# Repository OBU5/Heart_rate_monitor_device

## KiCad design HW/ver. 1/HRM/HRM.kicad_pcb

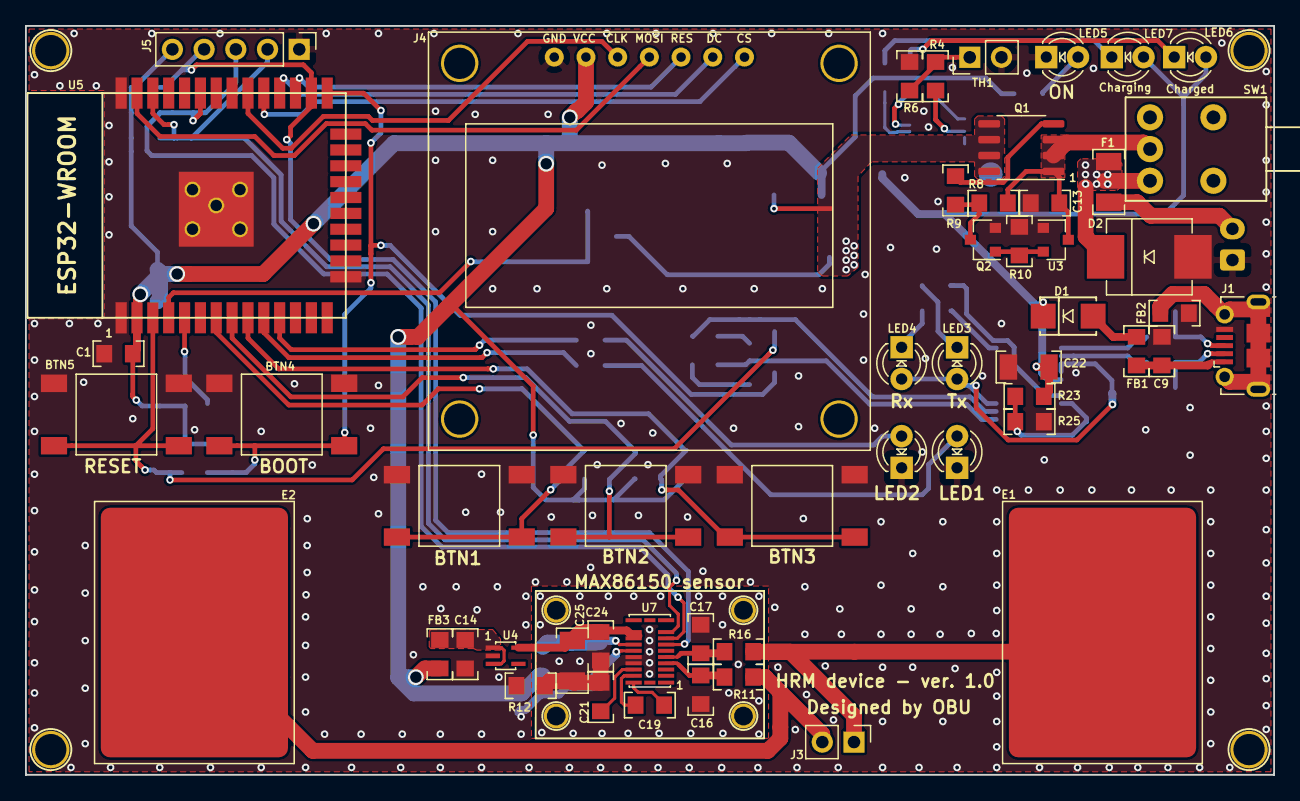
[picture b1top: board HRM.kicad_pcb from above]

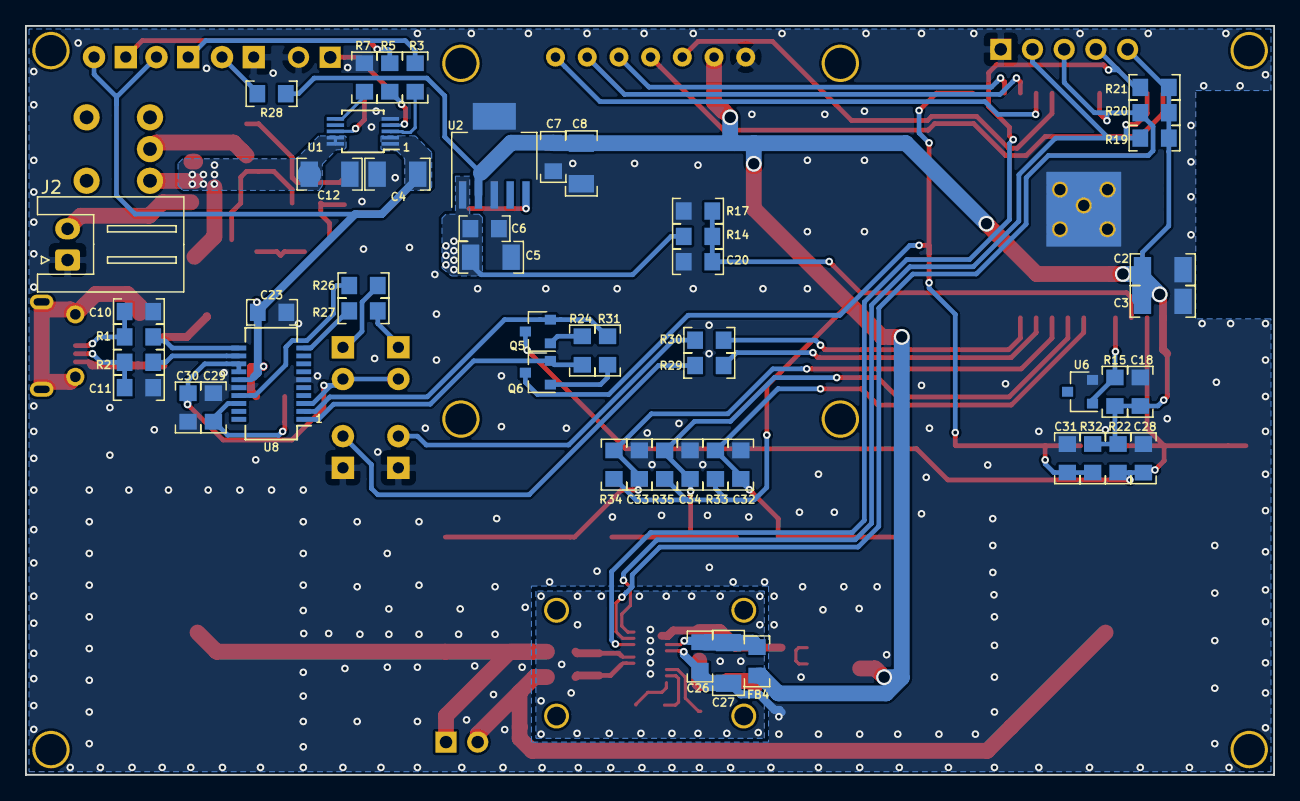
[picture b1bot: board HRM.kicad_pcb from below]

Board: 2 copper layers, 100.0 x 60.0 mm, 114 parts (53 on the bottom side), 65 nets.

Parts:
BTN1, BTN2, BTN3: user button; BTN_6x6mm
BTN4: BOOT; BTN_6x6mm
BTN5: RESET; BTN_6x6mm
C1, C6, C7, C13, C18, C20, C23, C24, C26, C28, C29, C30, C31, C32, C33, C34: 100n; C0805
C2, C3, C4, C5, C8, C12, C22, C25, C27: 10u; C1206
C9: 10n; C0805
C10, C11: 47p; C0805
C14, C19, C21: 1u; C0805
C16, C17: 10p; C0805
D1: D_Schottky; D_SMA
D2: 3A; D_SMC
E1: ECG_P; Electrode
E2: ECG_N; Electrode
F1: Fuse; R1206
FB1, FB2, FB3, FB4: Ferite bead; R0805
J1: USB_B_Micro; USB_Micro-B_Molex-105017-0001
J2: BATT; JST_XH_S2B-XH-A_1x02_P2.50mm_Horizontal
J3: Electrodes; PinHeader_1x02_P2.54mm_Vertical
J4: OLED; 1.3_inch_OLED
J5: I2C; PinHeader_1x05_P2.54mm_Vertical
J6, J8, J10, J12: Screw_Terminal_01x01; Screwh_hole-1.5mm
J7, J9, J11, J13: Screw_Terminal_01x01; Screwh_hole-2.5mm
LED1, LED2: User; LED-THT-3.0mm
LED3: TX; LED-THT-3.0mm
LED4: RX; LED-THT-3.0mm
LED5: Awake; LED-THT-3.0mm
LED6: Charged; LED-THT-3.0mm
LED7: Charging; LED-THT-3.0mm
Q1: PMOS-Si4403DDY; SO-8_3.9x4.9mm_P1.27mm
Q2: BSS138; SOT-23
Q5, Q6: BC847; SOT-23
R1, R2: 27; R0805
R3, R5: 470R; R0805
R4: 1.54k; R0805
R6: 69.8k; R0805
R7, R9, R26, R27, R28, R29, R30: 1k; R0805
R8, R10: 100k; R0805
R11, R16: 50k; R0805
R12: 0; R0805
R14: 13k; R0805
R15: 5k; R0805
R17: 24k; R0805
R19, R20, R21, R23, R24, R31: 4k7; R0805
R22, R25, R32, R33, R34, R35: 10k; R0805
SW1: Power; Switch_P-KNX125
TH1: NTC; PinHeader_1x02_P2.54mm_Vertical
U1: MCP73833-MSOP; MSOP-10_3x3mm_P0.5mm
U2: TPS73733; SOT-223-6
U3: TPS3839K33; SOT-23
U4: MAX8511; SC70-5pin
U5: ESP32-WROOM
U6: LM4040-2.5; SOT-23
U7: MAX86150; OLGA-22pin
U8: FT231XS; SSOP-20_3.9x8.7mm_P0.635mm

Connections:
3V3_IO: C30.2, LED3.2, LED4.2, U8.3, U8.13, U8.14
+1V8: C24.2, C25.2, U4.5, U7.13, U7.14
+3V3: C1.1, C2.1, C3.1, C7.2, C8.2, C18.2, FB3.2, FB4.1, J4.2, J5.5, R15.2, R19.1, R20.1, R21.1, R22.2, R28.2, R32.2, R33.2, R34.2, R35.2, U2.2, U5.2
+5VA: C4.1, C22.2, C23.2, D1.1, LED6.2, LED7.2, R23.2, U1.1, U1.2, U8.15
+BATT: C5.2, C6.2, Q1.5, Q1.6, Q1.7, Q1.8, R14.2, U2.1, U2.5
/BOOT: BTN4.2, C31.2, Q6.3, R32.1, U5.25
/DTR: Q6.2, R24.2, U8.1
/RESET: BTN5.2, C28.2, Q5.3, R22.1, U5.3
/RTS: Q5.2, R31.2, U8.2
/RX_LED: R27.1, U8.10
/TX_LED: R26.1, U8.17
/USBDM: R2.1, U8.12
/USBDP: R1.1, U8.11
/VBUS_SENSE: C29.1, R23.1, R25.2, U8.18
BAT_ADC: C20.2, R14.1, R17.2, U5.4
GNDA: C16.1, C17.2, C21.1, C24.1, C25.1, R12.1, U7.17, U7.18
GNDD: BTN1.1, BTN2.1, BTN3.1, BTN4.1, BTN5.1, C1.2, C2.2, C3.2, C4.2, C5.1, C6.1, C7.1, C8.1, C9.1, C10.1, C11.1, C12.2, C13.1, C14.1, C18.1, C20.1, C22.1, C23.1, C26.1, C27.1, C28.1, C29.2, C30.1, C31.1, C32.1, C33.1, C34.1, D2.2, FB2.2, J1.5, J2.1, J4.1, J5.1, LED1.1, LED2.1, LED5.1, Q2.2, R6.1, R7.1, R10.1, R12.2, R17.1, R25.1, TH1.2, U1.5, U2.3, U2.6, U3.1, U4.2, U5.1, U5.15, U5.38, U5.39, U6.2, U7.16, U8.6, U8.16
I2C_SCL: J5.2, R19.2, U5.36, U7.9
I2C_SDA: J5.3, R20.2, U5.33, U7.8
INTB: J5.4, R21.2, U5.26, U7.7
unnamed: C9.2, FB1.1, J1.1
unnamed: C10.2, J1.3, R1.2
unnamed: C11.2, J1.2, R2.2
unnamed: C12.1, D2.1, F1.2, SW1.1, U1.9, U1.10
unnamed: C13.2, Q1.1, Q1.2, Q1.3, R8.2, SW1.2, U3.3
unnamed: C14.2, FB3.1, U4.1, U4.3
unnamed: C16.2, R11.1, U7.4
unnamed: C17.1, R16.1, U7.5
unnamed: C19.1, U7.20
unnamed: C19.2, U7.21
unnamed: C21.2, U7.19
unnamed: C26.2, C27.2, FB4.2, U7.15
unnamed: D1.2, FB1.2
unnamed: E1.1, J3.1, R16.2
unnamed: E2.1, J3.2, R11.2
unnamed: F1.1, J2.2
unnamed: FB2.1, J1.6
unnamed: LED1.2, R29.1
unnamed: LED2.2, R30.1
unnamed: LED3.1, R26.2
unnamed: LED4.1, R27.2
unnamed: LED5.2, R28.1
unnamed: LED6.1, R5.2
unnamed: LED7.1, R3.2
unnamed: Q1.4, R9.1
unnamed: Q2.1, R10.2, U3.2
unnamed: Q2.3, R8.1, R9.2
unnamed: Q5.1, R24.1
unnamed: Q6.1, R31.1
unnamed: R3.1, U1.3
unnamed: R4.1, R6.2, TH1.1
unnamed: R4.2, U1.8
unnamed: R5.1, U1.4
unnamed: R7.2, U1.6
OLED_CLK: J4.3, U5.30
OLED_CS: J4.7, U5.29
OLED_DC: J4.6, U5.28
OLED_MOSI: J4.4, U5.37
OLED_RES: J4.5, U5.27
User_BTN1: BTN1.2, C32.2, R33.1, U5.7
User_BTN2: BTN2.2, C34.2, R35.1, U5.8
User_BTN3: BTN3.2, C33.2, R34.1, U5.9
User_LED1: R29.2, U5.10
User_LED2: R30.2, U5.11
V_ref: R15.1, U5.5, U6.1

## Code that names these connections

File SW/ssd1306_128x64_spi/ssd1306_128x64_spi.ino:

/**************************************************************************
 This is an example for our Monochrome OLEDs based on SSD1306 drivers

 Pick one up today in the adafruit shop!
 ------> http://www.adafruit.com/category/63_98

 This example is for a 128x64 pixel display using SPI to communicate
 4 or 5 pins are required to interface.

 Adafruit invests time and resources providing this open
 source code, please support Adafruit and open-source
 hardware by purchasing products from Adafruit!

 Written by Limor Fried/Ladyada for Adafruit Industries,
 with contributions from the open source community.
 BSD license, check license.txt for more information
 All text above, and the splash screen below must be
 included in any redistribution.
 **************************************************************************/

#include <SPI.h>
#include <Wire.h>
#include <Adafruit_GFX.h>
#include <Adafruit_SSD1306.h>

#define SCREEN_WIDTH 128 // OLED display width, in pixels
#define SCREEN_HEIGHT 64 // OLED display height, in pixels

// Declaration for SSD1306 display connected using software SPI (default case):
#define OLED_MOSI   23
#define OLED_CLK   18
#define OLED_DC    5
#define OLED_CS    -1
#define OLED_RESET 17
Adafruit_SSD1306 display(SCREEN_WIDTH, SCREEN_HEIGHT,
  OLED_MOSI, OLED_CLK, OLED_DC, OLED_RESET, OLED_CS);

/* Comment out above, uncomment this block to use hardware SPI
#define OLED_DC     6
#define OLED_CS     7
#define OLED_RESET  8
Adafruit_SSD1306 display(SCREEN_WIDTH, SCREEN_HEIGHT,
  &SPI, OLED_DC, OLED_RESET, OLED_CS);
*/

int hCenter = 32;                               // horizontal center of 64 / 2 = 32
int Radius = 30;                                // radius of circle
const float Pi = 3.14159265359;                 // Pi

#define NUMFLAKES     10 // Number of snowflakes in the animation example

#define LOGO_HEIGHT   16
#define LOGO_WIDTH    16
static const unsigned char PROGMEM logo_bmp[] =
{ B00000000, B11000000,
  B00000001, B11000000,
  B00000001, B11000000,
  B00000011, B11100000,
  B11110011, B11100000,
  B11111110, B11111000,
  B01111110, B11111111,
  B00110011, B10011111,
  B00011111, B11111100,
  B00001101, B01110000,
  B00011011, B10100000,
  B00111111, B11100000,
  B00111111, B11110000,
  B01111100, B11110000,
  B01110000, B01110000,
  B00000000, B00110000 };

void setup() {
  Serial.begin(9600);

  // SSD1306_SWITCHCAPVCC = generate display voltage from 3.3V internally
  if(!display.begin(SSD1306_SWITCHCAPVCC)) {
    Serial.println(F("SSD1306 allocation failed"));
    for(;;); // Don't proceed, loop forever
  } 
}

void loop(){

  display.drawRect(0, 0, 120, 64, WHITE);                      // draws border    
  int index = 0;
  for(int j = 0; j < 10; j ++){
    display.clearDisplay();                                      // clears display
    for (int i=0; i<120; i++){                                   // draws 120 pixels per loop
      index++;
      float Angle = index * 10;                                       // 120 X 3 = 360°
      int a = (hCenter + (sin(Angle * (Pi / 180)) * Radius));    // Pi/180 converts degrees to radians
      int b = (hCenter + (cos(Angle * (Pi / 180)) * Radius));    // Pi/180 converts degrees to radians
  
      display.drawPixel(i,a,WHITE);                              // draws each pixel for Sine wave
      display.display();                                         // displays new screen information
      delay(50);
    } 
  }
}

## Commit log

2021-02-26 Added more parts of schema design
2021-02-27 Added labels on MCU pins
2021-03-09 finished schema
2021-03-12 one of last schematic updates
2021-04-15 Design of PCB
2021-04-19 added script that prints sine wave on 1.3" OLED display
2021-04-20 Finally finished HW. Also added demo software and pictures of the device
    HW part is done. There was a problem with sensor soldering, but heat gun fixed it. Also demo software was implemented - only sends measured data in realtime. Also some photos of the PCB and measured 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
